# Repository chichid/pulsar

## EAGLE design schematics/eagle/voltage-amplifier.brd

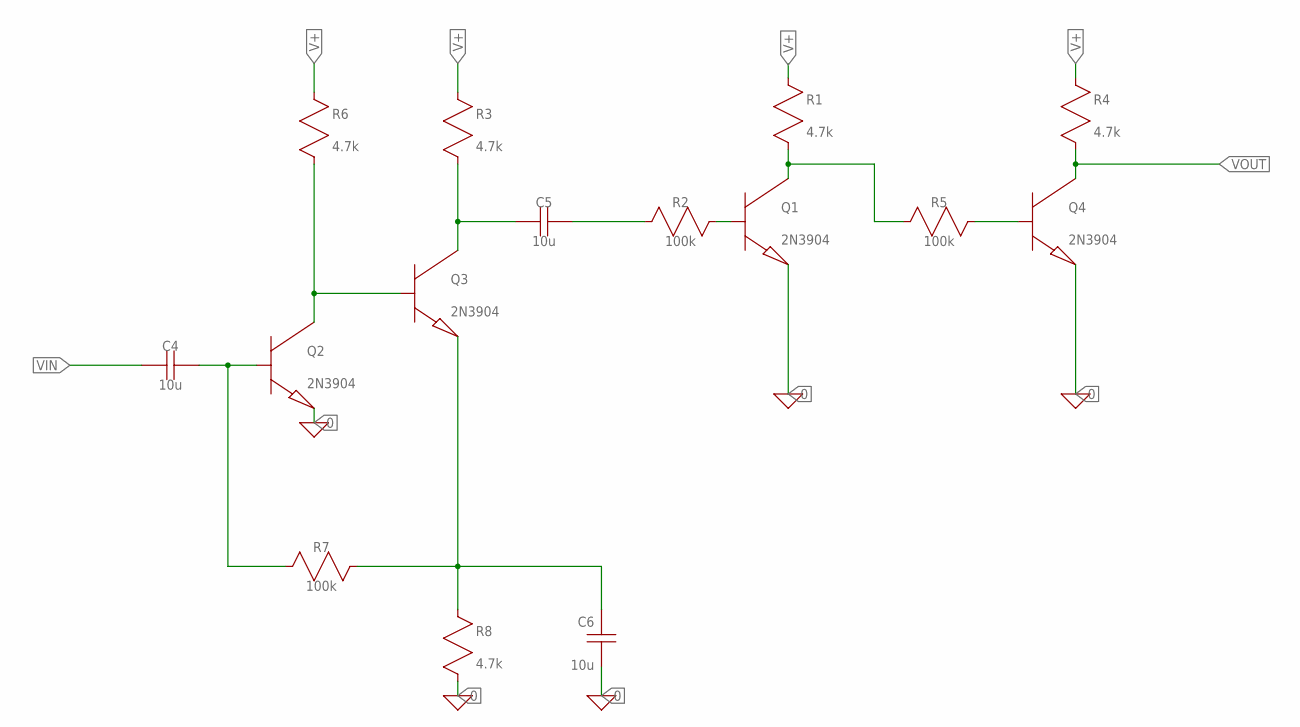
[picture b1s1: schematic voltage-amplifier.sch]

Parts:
C4, C5, C6: 10u; C050-025X075
Q1, Q2, Q3, Q4: 2N3904; TO92
R1, R3, R4, R6, R8: 4.7k; 0207/7
R2, R5, R7: 100k; 0309/10

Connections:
0: C6.1 (A), Q1.1 (E), Q2.1 (E), Q4.1 (E), R8.2 (B)
unnamed: Q4.2 (B), R5.1 (A)
unnamed: Q1.3 (C), R1.2 (B), R5.2 (B)
unnamed: C5.2 (B), Q3.3 (C), R3.2 (B)
unnamed: C5.1 (A), R2.2 (B)
unnamed: Q1.2 (B), R2.1 (A)
unnamed: Q2.3 (C), Q3.2 (B), R6.2 (B)
unnamed: C4.1 (A), Q2.2 (B), R7.2 (B)
unnamed: C6.2 (B), Q3.1 (E), R7.1 (A), R8.1 (A)
V+: R1.1 (A), R3.1 (A), R4.1 (A), R6.1 (A)
VIN: C4.2 (B)
VOUT: Q4.3 (C), R4.2 (B)

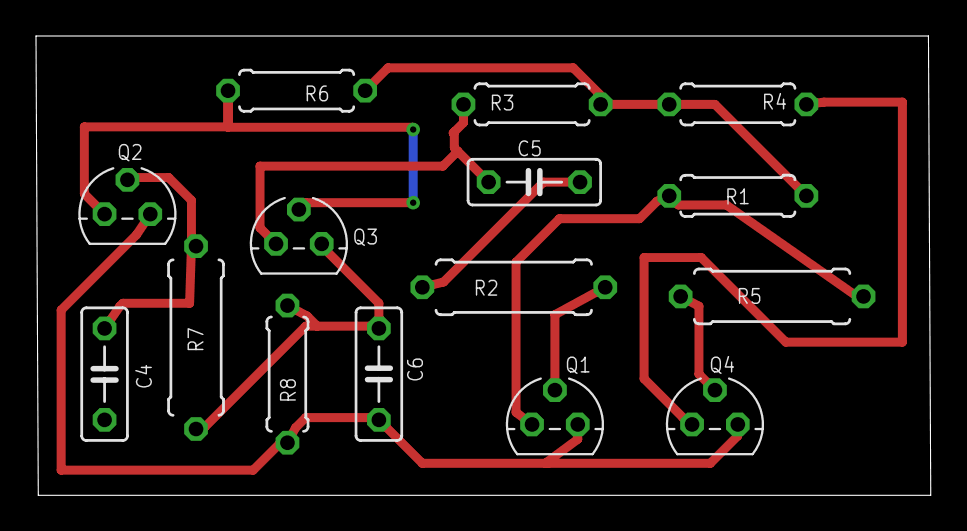
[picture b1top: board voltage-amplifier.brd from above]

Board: 2 copper layers, 49.7 x 25.5 mm, 15 parts (0 on the bottom side), 11 nets.

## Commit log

2020-12-09 Initialize project using Create React App
2020-12-09 Added Graph Library
2020-12-15 Pulsar Circuit
2020-12-16 Circuit Update
2020-12-16 Added The voltage amplifier
2020-12-16 Organized the graph
2020-12-16 Cleanup
2020-12-18 Buffer Implementation
2020-12-19 Pulsar npm package
2020-12-24 Pulsar NPM Library
2020-12-24 Schematics
2020-12-24 Added Eagle Schematics
2020-12-24 Optimized the voltage-amplifier PCB
2020-12-24 CLeanup .s files
2020-12-25 Voltage Amplifier PCB
2020-12-25 Increased Voltage Amplifier Spacing
2020-12-25 Changed package for the big resistances
